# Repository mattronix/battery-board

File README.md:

# PRC‑152A Repro — Battery / Radio Interface Boards

KiCad hardware project for the **battery-to-radio interface** of an AN/PRC‑152(A)
reproduction radio. It contains two small PCBs that mate through spring‑loaded
**pogo‑pin contacts**, plus a shared custom KiCad **footprint library** for those
mechanical contacts.

> All boards are designed in **KiCad 10** and built for fabrication/assembly at
> JLCPCB (Fabrication Toolkit export, JLCPCB BOM).

---

## Repository layout

```
battery-board/
├── Battery Top/                      # Board that sits on the battery
│   ├── Battery Top/                  # KiCad project (.kicad_pro/.kicad_sch/.kicad_pcb)
│   │   └── production/               # Gerbers/BOM/positions for JLCPCB
│   └── BOM/                          # JLCPCB BOM spreadsheet
├── Radio Bottom/                     # Board that sits on the radio body
│   └── Battery Bottom/               # KiCad project (folder name differs from board name)
├── Kicad Footprint Libaries/
│   └── Radio Library.pretty/         # ← the shared custom footprint library
└── README.md
```

> Note: a couple of folder names are inconsistent with the board names
> (`Radio Bottom/Battery Bottom/...`). The board you load is the `.kicad_pro`
> inside each, not the folder name.

---

## The two boards

### Battery Top
The interface board on the **battery** side. Carries power up to the radio and
exposes the data line.

| Ref | Part | Footprint | Purpose |
|-----|------|-----------|---------|
| J1 | JST XH 3‑pin vertical | `Connector_JST:...B3B-XH-A` | Battery power/data harness |
| J2, J3 | Pogo pin | `Radio Library:Pogo Battery 7MM` | VBAT+ contacts to radio |
| J5 | Pogo pin | `Radio Library:Pogo Battery 7MM` | DATA contact to radio |
| J4, J6 | Bolt pad | `Radio Library:Bolt Pad 4.25` | GND / M4 mounting bolt |
| F1 | 1206 fuse | `Fuse:Fuse_1206_3216Metric` | VBAT+ protection |

### Radio Bottom
The interface board on the **radio** side. It does battery current/power
monitoring and switches the load.

| Ref | Part | Footprint | Purpose |
|-----|------|-----------|---------|
| U1 | **INA226** power monitor | `Package_SO:MSOP-10_3x3mm` | I²C voltage/current/power sense |
| R1 | 5 mΩ shunt | `Resistor_SMD:R_2512_6332Metric` | Current‑sense resistor for U1 |
| Q1 | AOD403 / FQP27P06 P‑MOSFET | `Package_TO_SOT_SMD:TO-252-2` | Load switch / reverse protection |
| D1 | Zener | `Diode_SMD:D_SOD-123` | Gate / rail clamp |
| C1 | 0.1 µF 0603 | `Capacitor_SMD:C_0603` | Decoupling |
| R4 | 100 kΩ 0603 | `Resistor_SMD:R_0603` | Bias/pull |
| J1 | JST XH 6‑pin vertical | `Connector_JST:...B6B-XH-A` | Harness to radio |
| J2,J3 | Pogo pin | `Radio Library:Pogo Radio Bottom 6MM` | Power/data contacts from battery |
| J4,J6 | Bolt pad | `Radio Library:Bolt Pad 4.25` | GND / mounting bolt |

The two boards face each other: the **Pogo Battery 7MM** contacts on *Battery Top*
press onto the **Pogo Radio Bottom 6MM** contacts on *Radio Bottom*, carrying
VBAT+, GND and DATA across the mechanical joint. The INA226 + 5 mΩ shunt measure
battery current/voltage and report over the data line.

---

## Additional parts required (beyond the BOMs)

The electronic BOM spreadsheets (`*/BOM/*.xls`) cover the parts placed by JLCPCB.
You also need the following mechanical / assembly parts to build a working unit:

| Part | Spec / Source | Used on |
|------|---------------|---------|
| Battery | 1× — [AliExpress](https://www.aliexpress.com/item/1005009778488275.html) | Battery Top |
| O‑ring | 13.9 × 1.8 mm | Assembly seal |
| Stainless‑steel printed part | Metal (stainless) 3D print | Mechanical |
| Battery tabs | — | Battery Top |
| Pogo pin — Radio side, 6 mm height | [AliExpress](https://www.aliexpress.com/item/1005006095992803.html) | Radio Bottom (`Pogo Radio Bottom 6MM`) |
| Pogo pin — Battery side, 7 mm height | [AliExpress](https://www.aliexpress.com/item/32862727404.html) | Battery Top (`Pogo Battery 7MM`) |

---

## The custom footprint library (`Radio Library`)

`Kicad Footprint Libaries/Radio Library.pretty/` is a standard KiCad `.pretty`
footprint library — a folder of `.kicad_mod` files, one per footprint. It holds
the **non‑standard mechanical contacts** that aren't in KiCad's stock libraries.

| Footprint | Pad | Drill | Pad Ø | Used for |
|-----------|-----|-------|-------|----------|
| **Pogo Battery 7MM** | 1× THT circle | 1.6 mm | 2.5 mm | Pogo pin pressed from the battery side |
| **Pogo Radio Bottom 6MM** | 1× THT circle | 0.9 mm | 2.5 mm | Mating pogo target on the radio side |
| **Bolt Pad 4.25** | 1× THT circle | 4.3 mm | 7 mm | M4 mounting bolt + GND pad |

Each is a single through‑hole pad — these are mechanical/contact features rather
than multi‑pin parts, so the drill size is chosen to fit the specific pogo pin or
bolt.

> `*.kicad_mod.rsls` and `Untitled*` files in the library folder are editor
> scratch/temp artifacts and are not real footprints.

### How the boards find the library

Each project's `fp-lib-table` registers the library under the nickname
**`Radio Library`** via an **absolute path**:

```
(lib (name "Radio Library") (type "KiCad")
     (uri "/Users/.../PCB Design/Kicad Footprint Libaries/Radio Library.pretty"))
```

Footprints are then referenced as `Radio Library:<name>` (e.g.
`Radio Library:Pogo Battery 7MM`) in the PCBs.

⚠️ **The path is hard‑coded and absolute.** On another machine (or if you move the
repo) KiCad won't find the library and the custom footprints will show as
unresolved. Fix it one of two ways:

1. **Per project** — open *Preferences → Manage Footprint Libraries → Project*
   and re‑point the `Radio Library` row at this repo's
   `Kicad Footprint Libaries/Radio Library.pretty`, **or**
2. **Use a path variable** — define `KIPRJMOD`‑relative or a custom
   `${RADIO_LIB}` environment variable and edit each `fp-lib-table` to use it,
   so the project is portable.

---

## Working with the project

### Open in KiCad
Open the `.kicad_pro` inside `Battery Top/Battery Top/` or
`Radio Bottom/Battery Bottom/`. If footprints are unresolved, fix the
`Radio Library` path as described above.

### Re‑generate fabrication output
Each project has a `production/` folder (gerbers zip, `bom.csv`,
`positions.csv`, `designators.csv`) produced by the **Fabrication Toolkit**
plugin (settings in `fabrication-toolkit-options.json`). Re‑run the plugin after
PCB changes to refresh these, then upload the zip + BOM to JLCPCB.

---

## Contributing

Improvements are welcome. Open an issue for anything non‑trivial, keep pull
requests focused on one change, and re‑export the `production/` output if you
touch a PCB. See [`CONTRIBUTING.md`](CONTRIBUTING.md) for the full workflow and
guidelines.

## License

This project is licensed under the **CERN Open Hardware Licence Version 2 –
Weakly Reciprocal (CERN‑OHL‑W v2)** — see [`LICENSE`](LICENSE).

You are free to use, study, modify, share and manufacture these designs. Because
the licence is *weakly reciprocal*, if you **distribute modified versions** of
these boards you must make your modified design (source) files **available under
the same licence**. The boards may be incorporated into a larger product without
that product as a whole having to be open.

`SPDX-License-Identifier: CERN-OHL-W-2.0`

## Notes

- `.gitignore` only excludes `.DS_Store`. KiCad lock files (`~*.lck`), `.history/`
  editor backups, and `production/` outputs are currently committed — consider
  ignoring the first two.
- Footprint files carry KiCad 10 (`version 20260206`, `generator_version 10.0`);
  open with KiCad 10 or newer to avoid format warnings.

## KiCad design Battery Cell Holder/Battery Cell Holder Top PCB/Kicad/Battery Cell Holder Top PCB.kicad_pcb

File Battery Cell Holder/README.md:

# Battery Cell Holder

The cell pack of the PRC‑152A reproduction. Two stacked PCBs sandwich the
cylindrical cells: one board carries the spring contacts at each cell end, and
the pack feeds the *Battery Top* interface board. The custom **spring‑contact**
footprint library used by both boards lives here too.

## Layout

```
Battery Cell Holder/
├── Battery Cell Holder Top PCB/
│   └── Kicad/                 # KiCad 10 project — open Battery Cell Holder Top PCB.kicad_pro
├── Battery Cell Holder Bottom PCB/
│   └── Kicad/                 # KiCad 10 project — open Battery Cell Bottom PCB.kicad_pro
└── BatterySpringContact-kicad/   # shared custom symbol + footprint library (see its own README)
```

> Note: the bottom board's project file is named `Battery Cell Bottom PCB.*`
> while its folder is `Battery Cell Holder Bottom PCB/` — open the `.kicad_pro`,
> not the folder name.

## The two boards

Each board carries six battery spring contacts (`BT1`–`BT6`) plus solder‑wire
test points (`TP1`–`TP4`). The top and bottom boards face the opposite ends of
the cells so the springs press axially onto the cell terminals.

| Ref | Part | Footprint | Purpose |
|-----|------|-----------|---------|
| BT1–BT6 | Battery spring contact | `BatterySpringContact:Keystone_5222_SpringContact_THM` | Per‑cell end contacts |
| BT | Battery spring contact (plate) | `BatterySpringContact:BatteryContact_uxcell_Plate_TabSolder_18650` | Plate‑style contact variant |
| TP1–TP4 | Test point | `Connector_Wire:SolderWire-1.5sqmm_1x01_D1.7mm_OD3.9mm` | Wire solder / probe points |

These are generic mechanical contacts with **no LCSC part number**, so JLCPCB's
pick‑and‑place can't assemble them — the board is fabricated with the correct
land and you **hand‑solder** the contacts afterward.

## Footprint library

`BatterySpringContact-kicad/` is a standard KiCad symbol + `.pretty` footprint
library for the stamped 18650/AA spring contacts (coil‑spring negative end,
conical‑button positive end, plus a 7 mm conical PCB spring). It carries its own
detailed README — including footprint dimensions to measure, mounting notes, and
the 3D‑model setup. **Read [`BatterySpringContact-kicad/README.md`](BatterySpringContact-kicad/README.md) before editing the footprints.**

⚠️ The 7 mm conical PCB spring uses 0.3 mm wire — low current capacity. Fine for
sense/monitor paths; do **not** route high pack‑discharge current through it.

## Working with it

1. Open the `.kicad_pro` in **KiCad 10** or newer (one project per board).
2. If the `Battery_Spring_Contact` symbol or its footprints show as unresolved,
   register the `BatterySpringContact` symbol/footprint libraries under that
   nickname — see [`BatterySpringContact-kicad/README.md`](BatterySpringContact-kicad/README.md).
3. The footprint references the STEP model via `${KIPRJMOD}`, so copy the
   `.step`/`.wrl` next to the `.kicad_pcb` (or re‑point the 3D‑model path) for
   the 3D viewer.

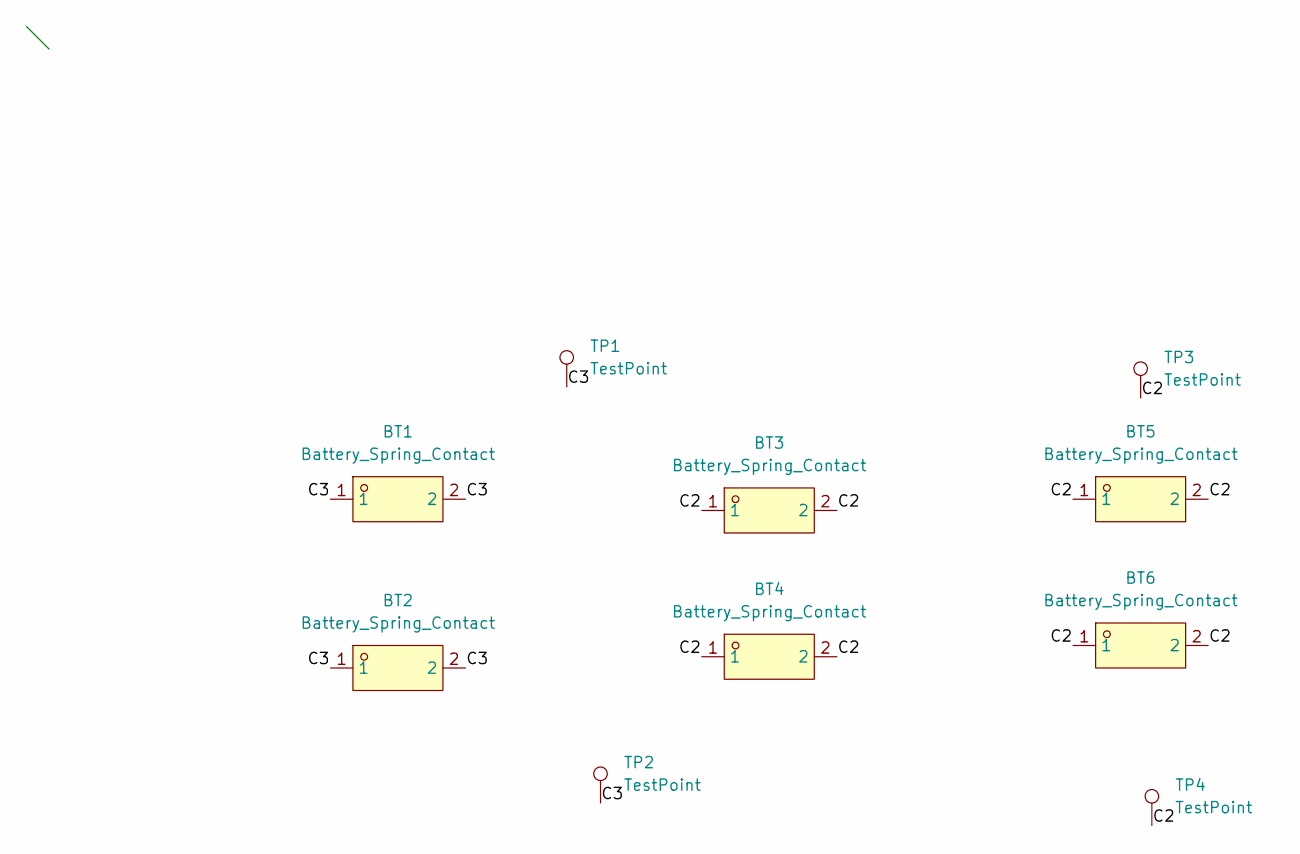
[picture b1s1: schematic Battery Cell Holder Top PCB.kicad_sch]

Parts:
BT1, BT2, BT3, BT4, BT5, BT6: Battery_Spring_Contact; TH-2_BD10.0_F10-12-0.5-1.3UU-SUS304; MPN F10-12-0.5-1.3UU-sus304; LCSC Part C19724688
TP1, TP2, TP3, TP4: TestPoint; SolderWire-1.5sqmm_1x01_D1.7mm_OD3.9mm

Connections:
/C2: BT3.1, BT3.2, BT4.1, BT4.2, BT5.1, BT5.2, BT6.1, BT6.2, TP3.1 (1_1), TP4.1 (1_1)
/C3: BT1.1, BT1.2, BT2.1, BT2.2, TP1.1 (1_1), TP2.1 (1_1)

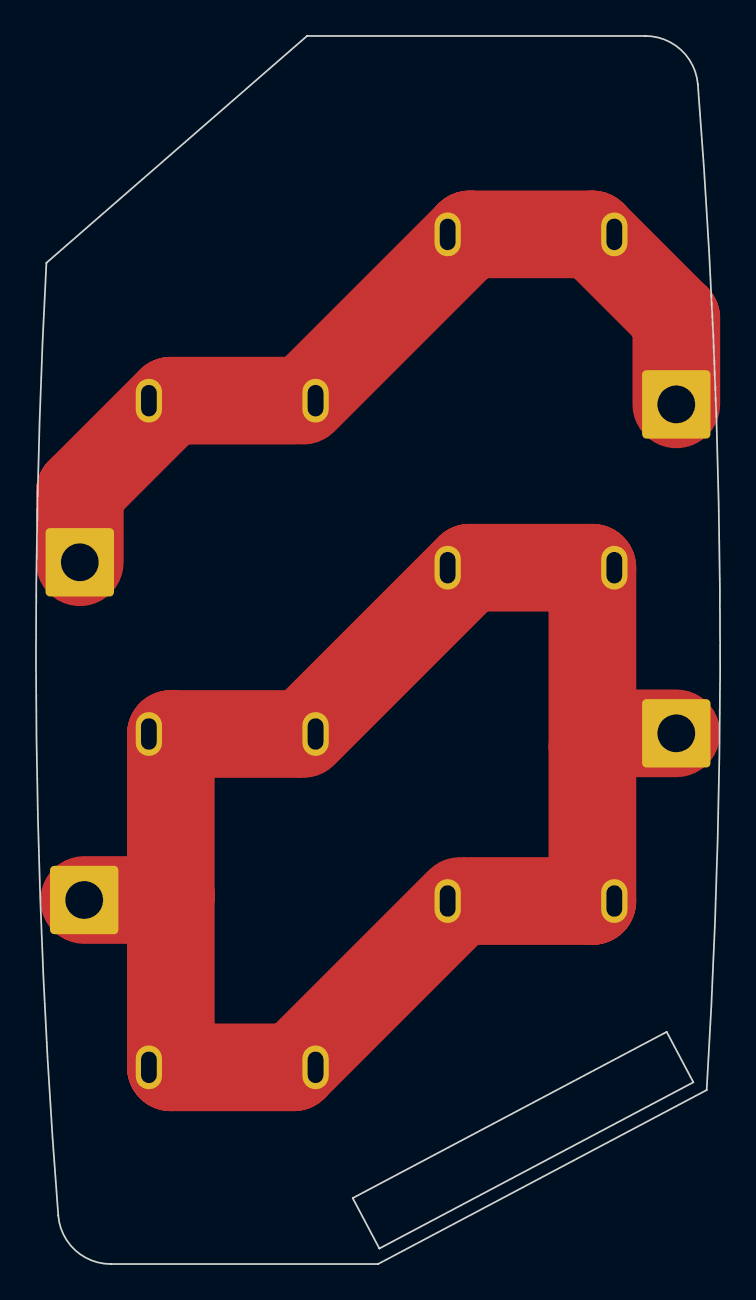
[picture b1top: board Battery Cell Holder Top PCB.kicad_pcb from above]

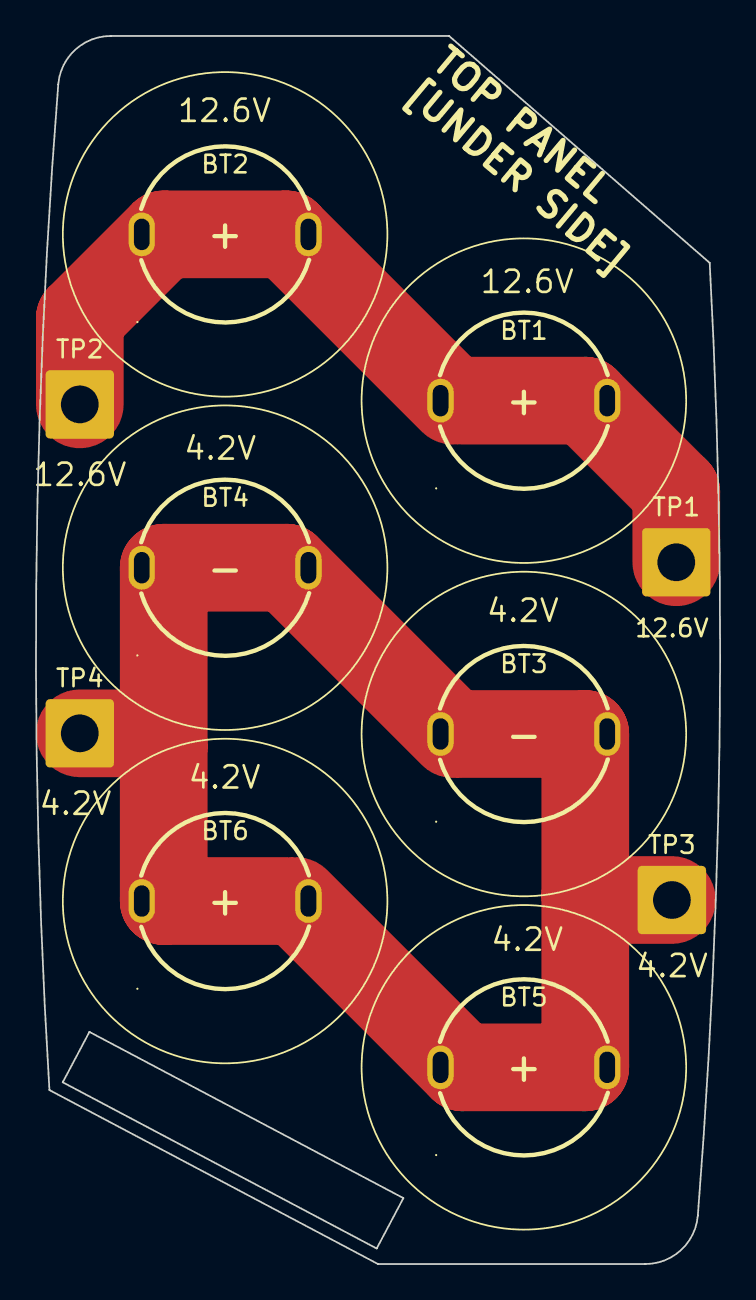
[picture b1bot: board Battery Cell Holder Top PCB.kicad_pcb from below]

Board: 2 copper layers, 39.0 x 70.0 mm, 10 parts (7 on the bottom side), 2 nets.

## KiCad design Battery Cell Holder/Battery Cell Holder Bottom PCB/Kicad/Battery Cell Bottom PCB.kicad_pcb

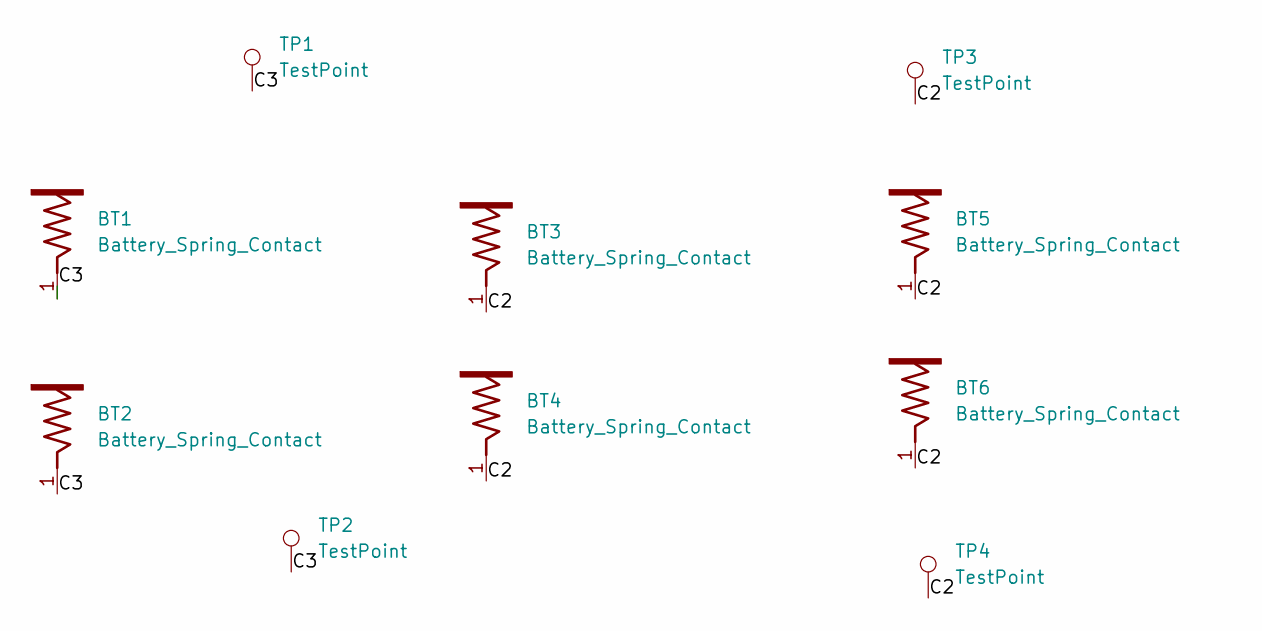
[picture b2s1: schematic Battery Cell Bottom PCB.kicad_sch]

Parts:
BT1, BT2, BT3, BT4, BT5, BT6: Battery_Spring_Contact; Keystone_5222_SpringContact_THM
TP1, TP2, TP3, TP4: TestPoint; SolderWire-1.5sqmm_1x01_D1.7mm_OD3.9mm

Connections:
/C2: BT3.1, BT4.1, BT5.1, BT6.1, TP3.1 (1_1), TP4.1 (1_1)
/C3: BT1.1, BT2.1, TP1.1 (1_1), TP2.1 (1_1)

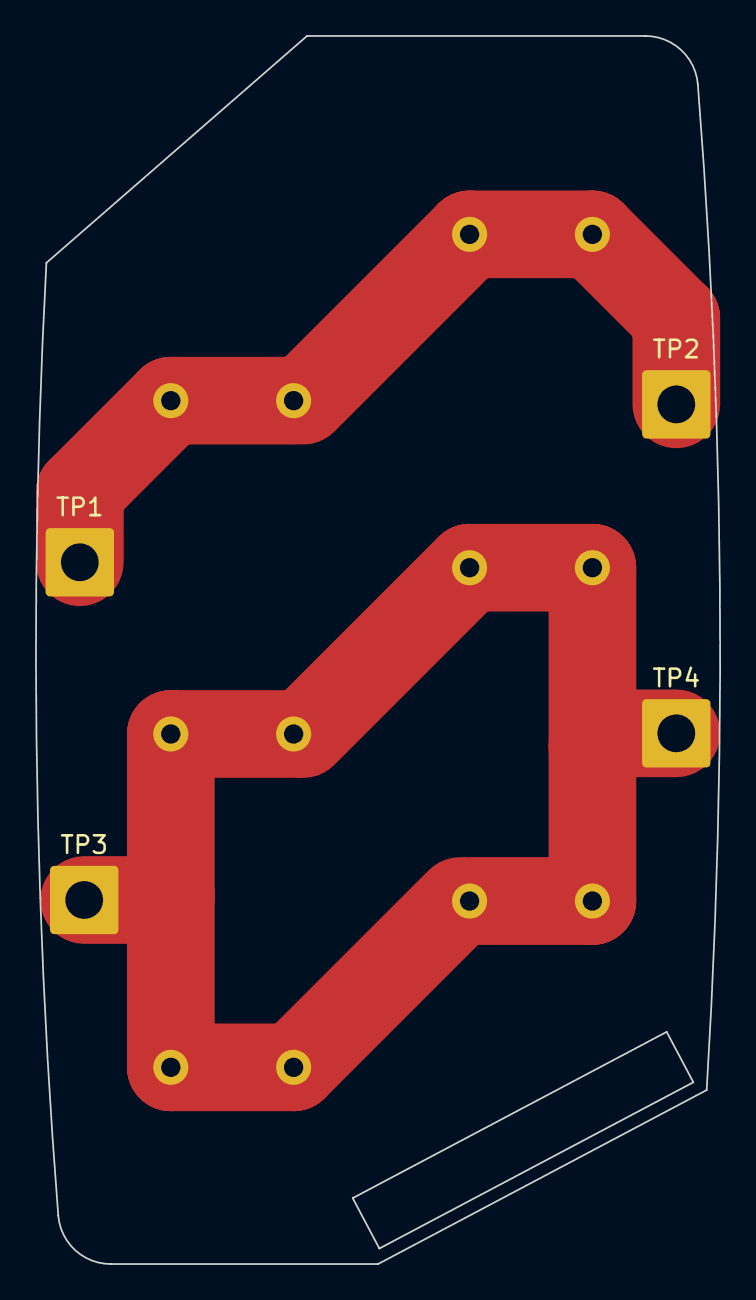
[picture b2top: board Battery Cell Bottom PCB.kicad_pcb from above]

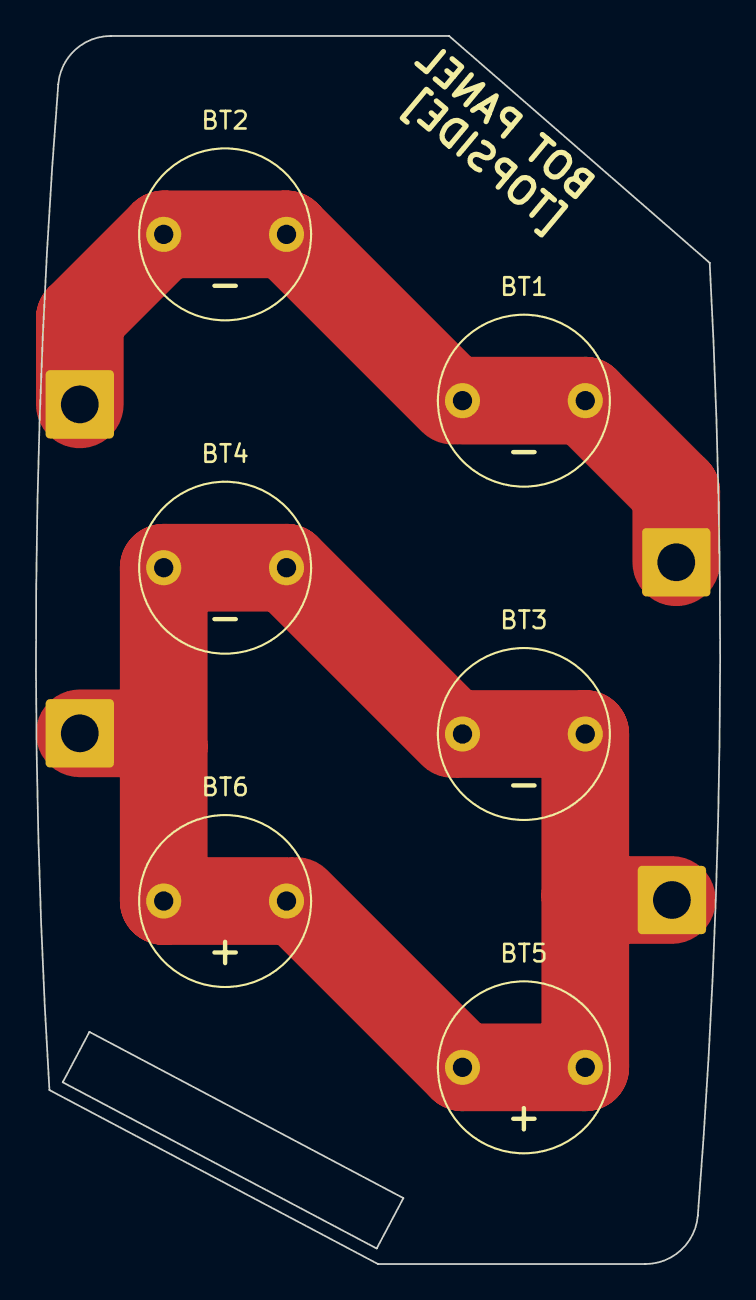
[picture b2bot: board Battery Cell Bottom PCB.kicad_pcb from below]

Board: 2 copper layers, 39.0 x 70.0 mm, 10 parts (6 on the bottom side), 2 nets.

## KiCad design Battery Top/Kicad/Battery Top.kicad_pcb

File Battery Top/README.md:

# Battery Top

Interface board on the **battery** side of the PRC‑152A reproduction. It carries
power up from the battery to the radio and exposes the data line, mating to
*Radio Bottom* through spring‑loaded pogo‑pin contacts.

## Layout

```
Battery Top/
├── Kicad/                 # KiCad 10 project — open Battery Top.kicad_pro here
│   ├── Battery Top.kicad_pro / .kicad_sch / .kicad_pcb / .kicad_dru
│   ├── fp-lib-table       # registers the shared "Radio Library" footprint lib
│   ├── fabrication-toolkit-options.json
│   └── production/        # JLCPCB output (gerbers zip, BOM, positions) — git-ignored
└── BOM/
    └── JLPCB BOM v1.xls   # JLCPCB BOM spreadsheet
```

## Key components

| Ref | Part | Footprint | Purpose |
|-----|------|-----------|---------|
| J1 | JST XH 3‑pin vertical | `Connector_JST:...B3B-XH-A` | Battery power/data harness |
| J2, J3 | Pogo pin | `Radio Library:Pogo Battery 7MM` | VBAT+ contacts to radio |
| J5 | Pogo pin | `Radio Library:Pogo Battery 7MM` | DATA contact to radio |
| J4, J6 | Bolt pad | `Radio Library:Bolt Pad 4.25` | GND / M4 mounting bolt |
| F1 | 1206 fuse | `Fuse:Fuse_1206_3216Metric` | VBAT+ protection |

The **Pogo Battery 7MM** contacts here press onto the **Pogo Radio Bottom 6MM**
targets on *Radio Bottom*, carrying VBAT+, GND and DATA across the joint.

## Working with it

1. Open `Kicad/Battery Top.kicad_pro` in **KiCad 10** or newer.
2. If the custom pogo/bolt footprints show as unresolved, re‑point the
   `Radio Library` entry — see [`../Kicad Footprint Libaries/README.md`](../Kicad%20Footprint%20Libaries/README.md).
3. After PCB changes, re‑run the **Fabrication Toolkit** plugin to refresh
   `production/`, then upload the zip + BOM to JLCPCB.

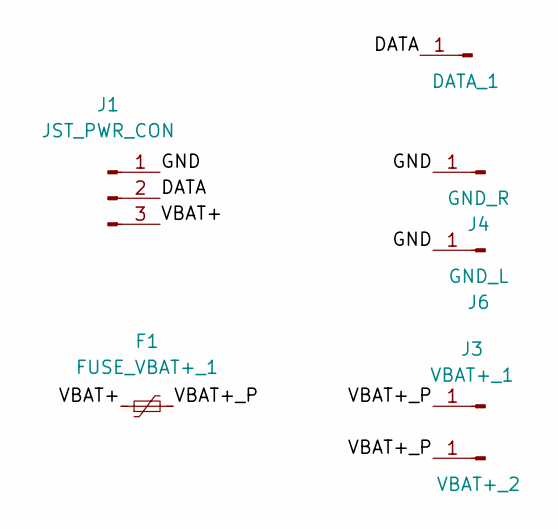
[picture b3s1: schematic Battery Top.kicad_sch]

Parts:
F1: FUSE_VBAT+_1; R_1812_4532Metric
J1: JST_PWR_CON; JST_XH_B3B-XH-A_1x03_P2.50mm_Vertical
J2: VBAT+_2; Pogo Battery 7MM
J3: VBAT+_1; Pogo Battery 7MM
J4: GND_R; Bolt Pad 4.25
J5: DATA_1; Pogo Battery 7MM
J6: GND_L; Bolt Pad 4.25

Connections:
/DATA: J1.2, J5.1 (Pin_1_1)
/GND: J1.1, J4.1 (Pin_1_1), J6.1 (Pin_1_1)
/VBAT+: F1.1, J1.3
/VBAT+_P: F1.2, J2.1 (Pin_1_1), J3.1 (Pin_1_1)

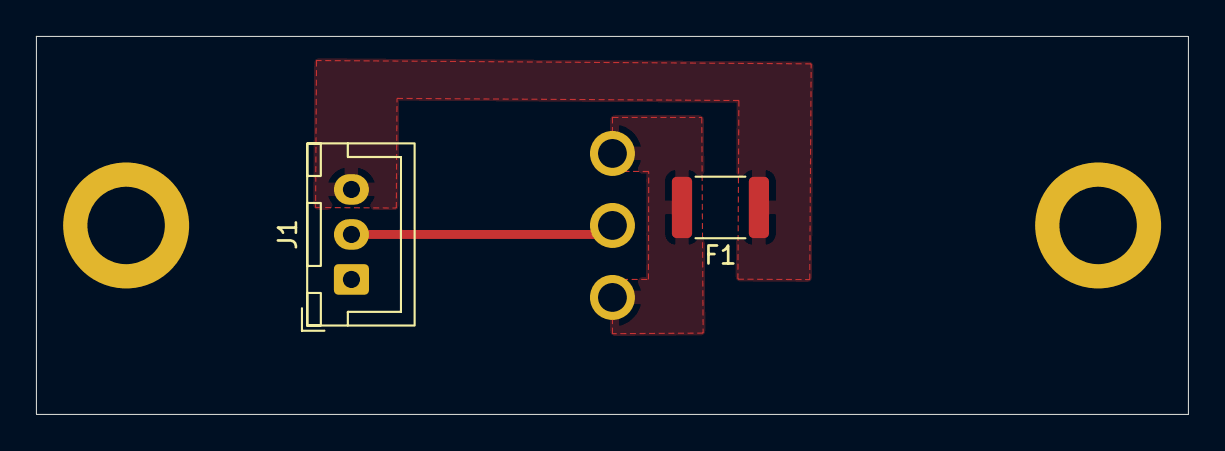
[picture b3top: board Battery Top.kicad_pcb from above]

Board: 2 copper layers, 64.0 x 21.0 mm, 7 parts (0 on the bottom side), 4 nets.

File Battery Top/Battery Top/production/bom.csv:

Designator,Footprint,Quantity,Value,LCSC Part #
F1,1206,1,FUSE_VBAT+_1,
J1,JST_XH_B3B-XH-A_1x03_P2.50mm_Vertical,1,JST_PWR_CON,
J2,Pogo Battery 7MM,1,VBAT+_2,
J3,Pogo Battery 7MM,1,VBAT+_1,
J4,Bolt Pad 4.25,1,GND_R,
J5,Pogo Battery 7MM,1,DATA_1,
J6,Bolt Pad 4.25,1,GND_L,

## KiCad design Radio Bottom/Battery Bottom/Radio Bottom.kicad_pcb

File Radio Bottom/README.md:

# Radio Bottom

Interface board on the **radio** side of the PRC‑152A reproduction. It does
battery voltage/current/power monitoring (INA226 + shunt) and switches the load,
mating to *Battery Top* through spring‑loaded pogo‑pin contacts.

## Layout

```
Radio Bottom/
├── Kicad/                  # KiCad 10 project — open Radio Bottom.kicad_pro here
│   ├── Radio Bottom.kicad_pro / .kicad_sch / .kicad_pcb / .kicad_dru
│   ├── fp-lib-table        # registers the shared "Radio Library" footprint lib
│   └── fabrication-toolkit-options.json
└── BOM/
    └── Radio Bottom BOM V1.xls   # JLCPCB BOM spreadsheet
```

## Key components

| Ref | Part | Footprint | Purpose |
|-----|------|-----------|---------|
| U1 | **INA226** power monitor | `Package_SO:MSOP-10_3x3mm` | I²C voltage/current/power sense |
| R1 | 5 mΩ shunt | `Resistor_SMD:R_2512_6332Metric` | Current‑sense resistor for U1 |
| Q1 | AOD403 / FQP27P06 P‑MOSFET | `Package_TO_SOT_SMD:TO-252-2` | Load switch / reverse protection |
| D1 | Zener | `Diode_SMD:D_SOD-123` | Gate / rail clamp |
| C1 | 0.1 µF 0603 | `Capacitor_SMD:C_0603` | Decoupling |
| R4 | 100 kΩ 0603 | `Resistor_SMD:R_0603` | Bias/pull |
| J1 | JST XH 6‑pin vertical | `Connector_JST:...B6B-XH-A` | Harness to radio |
| J2, J3 | Pogo pin | `Radio Library:Pogo Radio Bottom 6MM` | Power/data contacts from battery |
| J4, J6 | Bolt pad | `Radio Library:Bolt Pad 4.25` | GND / mounting bolt |

The **Pogo Radio Bottom 6MM** targets here receive the **Pogo Battery 7MM**
contacts from *Battery Top*. The INA226 + 5 mΩ shunt measure battery
current/voltage and report over the data line.

## Working with it

1. Open `Kicad/Radio Bottom.kicad_pro` in **KiCad 10** or newer.
2. If the custom pogo/bolt footprints show as unresolved, re‑point the
   `Radio Library` entry — see [`../Kicad Footprint Libaries/README.md`](../Kicad%20Footprint%20Libaries/README.md).
3. After PCB changes, re‑run the **Fabrication Toolkit** plugin to refresh the
   fabrication output, then upload the zip + BOM to JLCPCB.

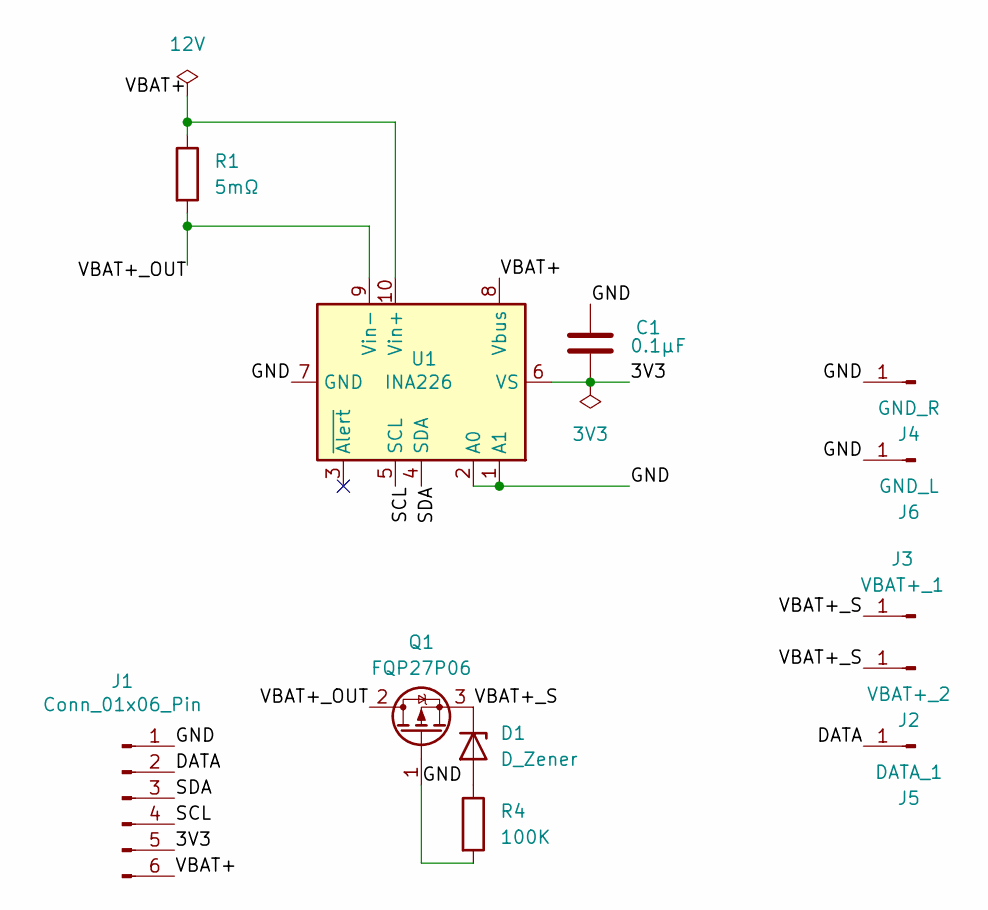
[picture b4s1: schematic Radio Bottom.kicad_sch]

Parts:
C1: 0.1µF; C_0603_1608Metric
D1: D_Zener; D_SOD-123
J1: Conn_01x06_Pin; JST_XH_B6B-XH-A_1x06_P2.50mm_Vertical
J2: VBAT+_2; Pogo Radio Bottom 6MM
J3: VBAT+_1; Pogo Radio Bottom 6MM
J4: GND_R; Bolt Pad 4.25
J5: DATA_1; Pogo Radio Bottom 6MM
J6: GND_L; Bolt Pad 4.25
Q1: FQP27P06; TO-252-2
R1: 5mΩ; R_2512_6332Metric
R4: 100K; R_0603_1608Metric
U1: INA226; MSOP-10_3x3mm_P0.5mm

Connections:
/3V3: C1.2, J1.5, U1.6 (VS)
/DATA: J1.2, J5.1 (Pin_1_1)
/GND: C1.1, J1.1, J4.1 (Pin_1_1), J6.1 (Pin_1_1), Q1.1 (G), R4.2, U1.1 (A1), U1.2 (A0), U1.7 (GND)
/SCL: J1.4, U1.5 (SCL)
/SDA: J1.3, U1.4 (SDA)
/VBAT+: J1.6, R1.1, U1.8 (Vbus), U1.10 (Vin+)
/VBAT+_OUT: Q1.2 (D), R1.2, U1.9 (Vin-)
/VBAT+_S: D1.1 (K), J2.1 (Pin_1_1), J3.1 (Pin_1_1), Q1.3 (S)
unnamed: D1.2 (A), R4.1

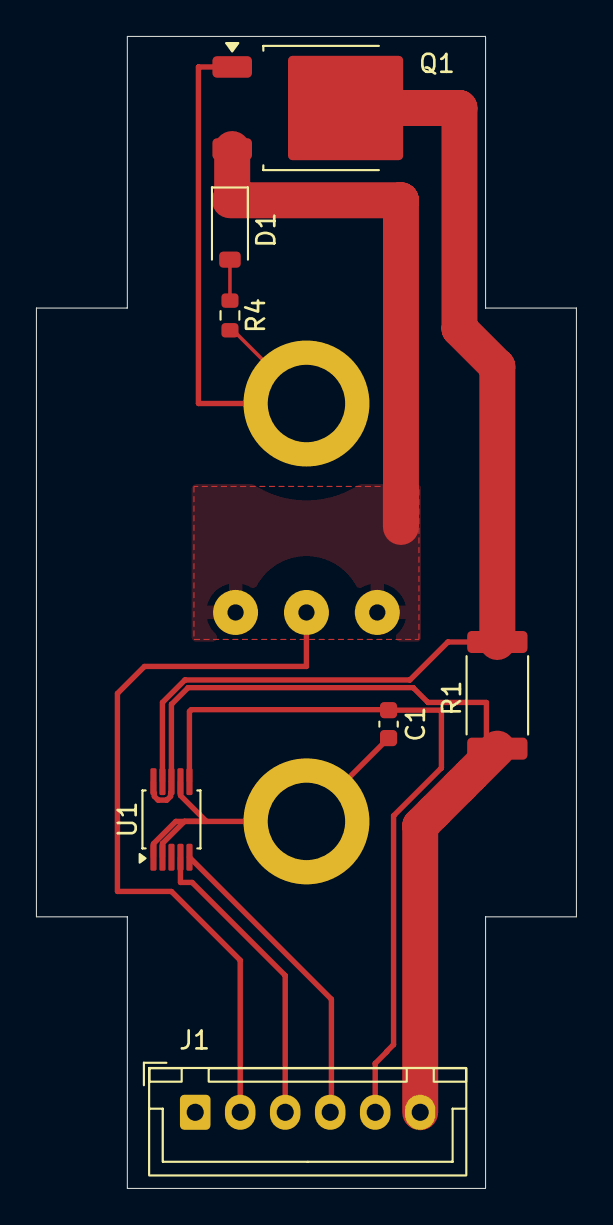
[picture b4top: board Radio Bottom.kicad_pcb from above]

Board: 2 copper layers, 30.0 x 64.0 mm, 12 parts (0 on the bottom side), 9 nets.

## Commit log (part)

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2026-06-05 base
2026-06-05 useless files
2026-06-05 readme
2026-06-06 fixed footprint for fuse
2026-06-06 layout
2026-06-07 footprint
2026-06-10 battery board
2026-06-10 fixes
2026-06-10 fixes to boards
2026-06-10 fabrication + 3d model of custom battery holder
2026-06-10 fusion files for customer board
2026-06-11 added full model rendering
2026-06-24 fixed
2026-06-25 snug fit
2026-06-25 charger
